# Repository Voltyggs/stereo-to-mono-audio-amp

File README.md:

# stereo-to-mono-audio-amp

to use this, cut off a earphone, or any stereo audio output, solder the left and right stereo terminal into the appropriate smd pads, and for the speaker, same as the earphone, solder the +- terminals into the +- output. and power into the power terminals. As a result you should get a amplified mono audio! :D

BOM at the bottom <br />

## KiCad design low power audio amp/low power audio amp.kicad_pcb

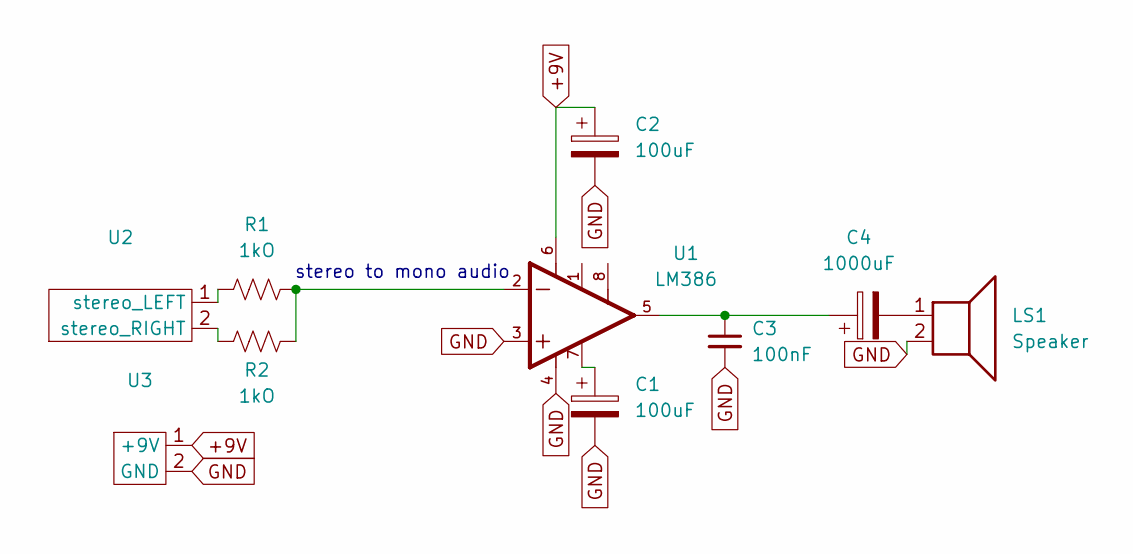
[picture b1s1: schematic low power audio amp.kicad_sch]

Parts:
C1, C2: 100uF; CP_Radial_D5.0mm_P2.00mm
C3: 100nF; CP_Radial_D5.0mm_P2.50mm
C4: 1000uF; CP_Radial_D10.0mm_P5.00mm
LS1: Speaker; 2_3W_8O_Speaker
R1, R2: 1kO; R_Axial_DIN0204_L3.6mm_D1.6mm_P7.62mm_Horizontal
U1: LM386; DIP08
U2: earphone_stereo
U3: Power

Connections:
+9V: C2.1, U1.6, U3.1 (+9V)
GND: C1.2, C2.2, C3.2, LS1.2, U1.3, U1.4, U3.2 (GND)
unnamed: C1.1, U1.7
unnamed: C3.1, C4.1, U1.5
unnamed: C4.2, LS1.1
unnamed: R1.2, R2.1, U1.2
unnamed: R1.1, U2.1 (stereo_LEFT)
unnamed: R2.2, U2.2 (stereo_RIGHT)

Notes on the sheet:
stereo to mono audio

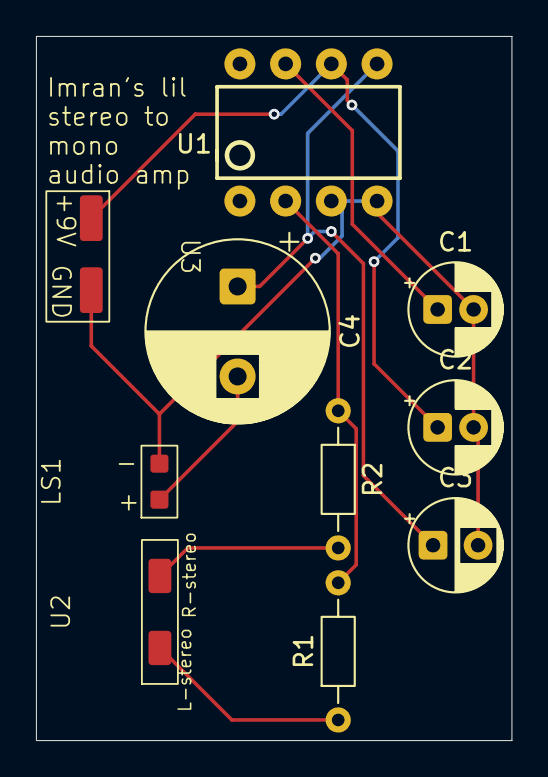
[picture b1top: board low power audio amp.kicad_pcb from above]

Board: 2 copper layers, 26.4 x 39.1 mm, 10 parts (0 on the bottom side), 8 nets.

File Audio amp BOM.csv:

Items,Description,Qty,BD Price (Taka),BD URL,Pack Size,US Price (USD),US URL,Pack Size
LM836 IC,Operational Amplifier,1,20,https://techshopbd.com/product/lm386-opamp,1,7,https://www.amazon.com/BOJACK-LM358P-Operational-Amplifier-L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,50
100nF / 0.1uF capacitor,Ceramic Capacitor,1,0.15,https://techshopbd.com/product/ceramic-capacitor-104-100nf,10,0.07,https://www.amazon.com/mxuteuk-Multilayer-Monolithic-Capacit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,120
100uF capacitor,Electrolytic Capacitor,2,3.89,https://techshopbd.com/product/100uf-50v-capacitor,1,6,https://www.amazon.com/Tnisesm-Electrolytic-Capacitor-Alumin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,20
1000uF capacitor,Electrolytic Capacitor,1,18.06,https://techshopbd.com/product/1000uf-50v-capacitor,1,6,https://www.amazon.com/ALLECIN-Electrolytic-Capacitor-0-39x0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,10
1K Ohm resistor,Resistor,2,3.02,https://techshopbd.com/product/1k-ohm-2w-resistor,1,6,https://www.amazon.com/EDGELEC-Resistor-Tolerance-Multiple-R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,100
Speaker,Loudspeaker,1,260.06,https://techshopbd.com/product/stereo-enclosed-speaker-3w-4-ohm,1,5,https://www.amazon.com/Loudspeakers-JST-PH2-0-Interface-Elec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,1
Earphone/Stereo Input,Audio Input,1,120,https://www.daraz.com.bd/products/u19-wired-stereo-earphones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,1,1,https://www.amazon.com/Skullcandy-Effortless-Sound-Earbuds-S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,1
,,,,,,,,
FINAL PRICE FOR ITEMS:,,,425.18,,,31.07,,

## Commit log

2025-12-11 Update README with usage instructions
    Added usage instructions for the audio amplifier.
2025-12-11 Update README with BOM and images
    Added Bill of Materials (BOM) and images for the project.
2025-12-11 Revise BOM with prices and purchase links
    Updated the Bill of Materials (BOM) section with pricing and links for components.
2025-12-11 Change currency from cents to USD in BOM
    Updated pricing information for various components.
2025-12-11 Modify BOM with updated pack sizes and prices
    Updated the pack size for Earphone/Stereo Input and adjusted the final price for items.
